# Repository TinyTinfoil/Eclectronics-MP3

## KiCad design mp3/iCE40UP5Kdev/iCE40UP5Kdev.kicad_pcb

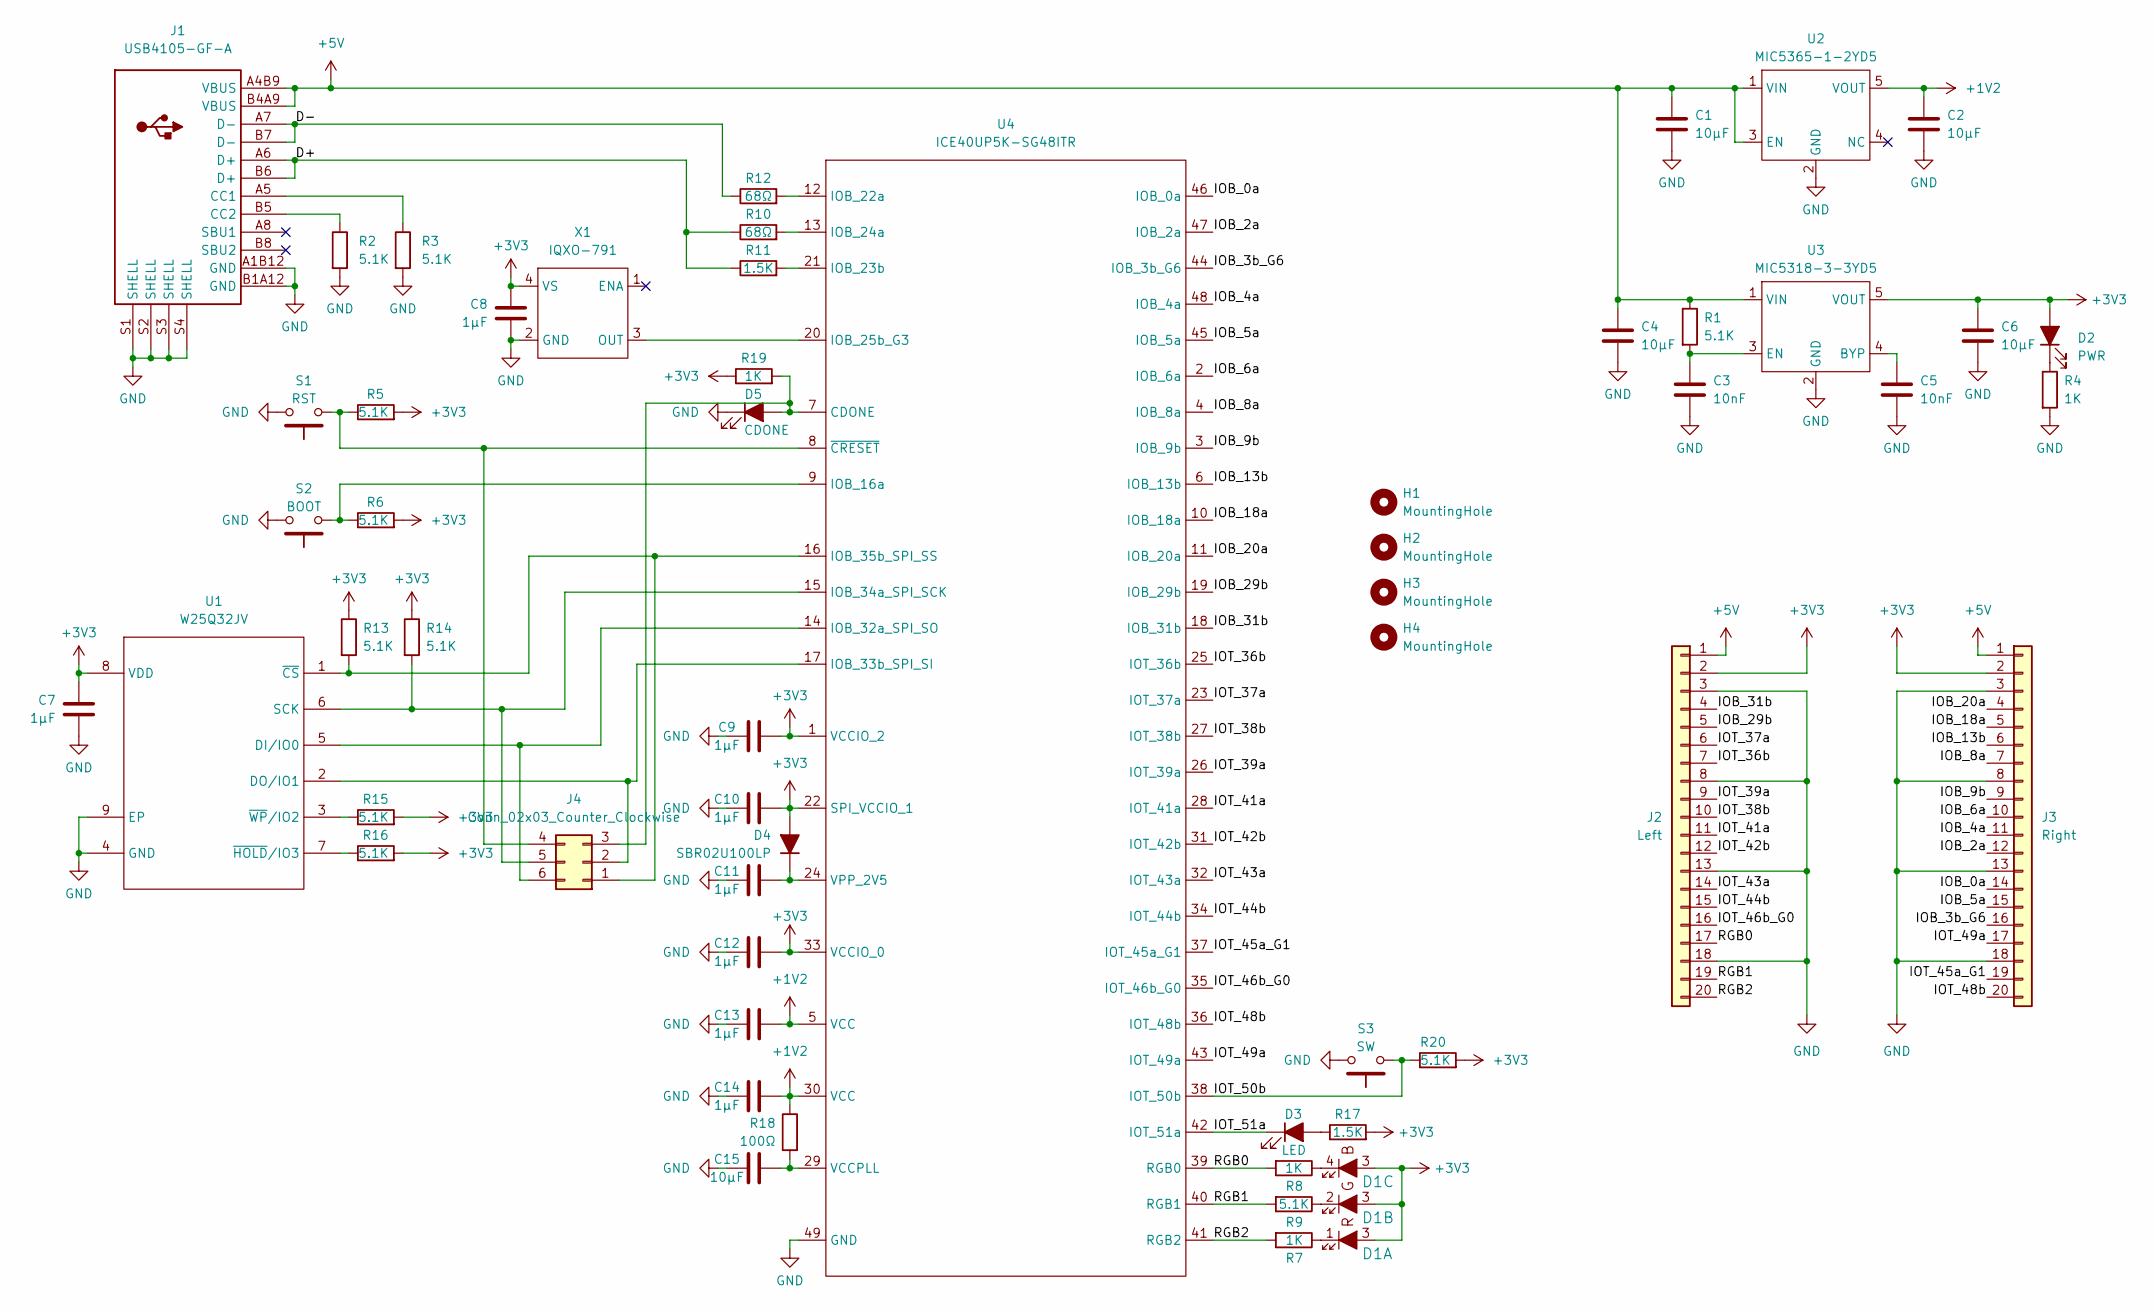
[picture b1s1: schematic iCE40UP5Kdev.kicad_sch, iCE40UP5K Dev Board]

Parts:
C1, C2, C4, C6, C15: 10µF; C_0603_1608Metric
C3, C5: 10nF; C_0402_1005Metric
C7, C8, C9, C10, C11, C12, C13, C14: 1µF; C_0402_1005Metric
D1: IN-S85TATRGB_ALT; IN-S85TATRGB
D2: PWR; LED_0805_2012Metric
D3: LED; LED_0805_2012Metric
D4: SBR02U100LP; D_0402_1005Metric
D5: CDONE; LED_0805_2012Metric
H1, H2, H3, H4: MountingHole; ToolingHole_1.152mm
J1: USB4105-GF-A
J2: Left; PinHeader_1x20_P2.54mm_Vertical
J3: Right; PinHeader_1x20_P2.54mm_Vertical
J4: Conn_02x03_Counter_Clockwise; PinHeader_2x03_P2.54mm_Vertical
R1, R2, R3, R5, R6, R9, R13, R14, R15, R16, R20: 5.1K; R_0402_1005Metric
R4, R7, R8, R19: 1K; R_0402_1005Metric
R10, R12: 68Ω; R_0402_1005Metric
R11, R17: 1.5K; R_0402_1005Metric
R18: 100Ω; R_0402_1005Metric
S1: RST; SW_SPST_B3U-1000P
S2: BOOT; SW_SPST_B3U-1000P
S3: SW; SW_SPST_B3U-1000P
U1: W25Q32JV; WSON-8-1EP_6x5mm_P1.27mm_EP3.4x4.3mm
U2: MIC5365-1-2YD5; TSOT-23-5
U3: MIC5318-3-3YD5; TSOT-23-5
U4: ICE40UP5K-SG48ITR; QFN-48-1EP_7x7mm_P0.5mm_EP5.3x5.3mm
X1: IQXO-791

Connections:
+1V2: C2.1, C13.2, C14.2, R18.1, U2.5 (VOUT), U4.5 (VCC), U4.30 (VCC)
+3V3: C6.1, C7.1, C8.1, C9.2, C10.2, C12.2, D1.3, D2.2 (A), D4.2 (A), J2.2, J3.2, R5.2, R6.2, R13.1, R14.1, R15.2, R16.2, R17.2, R19.1, R20.2, U1.8 (VDD), U3.5 (VOUT), U4.1 (VCCIO_2), U4.22 (SPI_VCCIO_1), U4.33 (VCCIO_0), X1.4 (VS)
+5V: C1.1, C4.1, J1.A4B9 (VBUS), J1.B4A9 (VBUS), J2.1, J3.1, R1.1, U2.1 (VIN), U2.3 (EN), U3.1 (VIN)
/D+: J1.A6 (D+), J1.B6 (D+), R10.1, R11.1
/D-: J1.A7 (D-), J1.B7 (D-), R12.1
/IOB_0a: J3.14, U4.46 (IOB_0a)
/IOB_2a: J3.12, U4.47 (IOB_2a)
/IOB_3b_G6: J3.16, U4.44 (IOB_3b_G6)
/IOB_4a: J3.11, U4.48 (IOB_4a)
/IOB_5a: J3.15, U4.45 (IOB_5a)
/IOB_6a: J3.10, U4.2 (IOB_6a)
/IOB_8a: J3.7, U4.4 (IOB_8a)
/IOB_9b: J3.9, U4.3 (IOB_9b)
/IOB_13b: J3.6, U4.6 (IOB_13b)
/IOB_18a: J3.5, U4.10 (IOB_18a)
/IOB_20a: J3.4, U4.11 (IOB_20a)
/IOB_29b: J2.5, U4.19 (IOB_29b)
/IOB_31b: J2.4, U4.18 (IOB_31b)
/IOT_36b: J2.7, U4.25 (IOT_36b)
/IOT_37a: J2.6, U4.23 (IOT_37a)
/IOT_38b: J2.10, U4.27 (IOT_38b)
/IOT_39a: J2.9, U4.26 (IOT_39a)
/IOT_41a: J2.11, U4.28 (IOT_41a)
/IOT_42b: J2.12, U4.31 (IOT_42b)
/IOT_43a: J2.14, U4.32 (IOT_43a)
/IOT_44b: J2.15, U4.34 (IOT_44b)
/IOT_45a_G1: J3.19, U4.37 (IOT_45a_G1)
/IOT_46b_G0: J2.16, U4.35 (IOT_46b_G0)
/IOT_48b: J3.20, U4.36 (IOT_48b)
/IOT_49a: J3.17, U4.43 (IOT_49a)
/IOT_50b: R20.1, S3.1, U4.38 (IOT_50b)
/IOT_51a: D3.1 (K), U4.42 (IOT_51a)
/RGB0: J2.17, R8.2, U4.39 (RGB0)
/RGB1: J2.19, R9.2, U4.40 (RGB1)
/RGB2: J2.20, R7.2, U4.41 (RGB2)
GND: C1.2, C2.2, C3.2, C4.2, C5.2, C6.2, C7.2, C8.2, C9.1, C10.1, C11.1, C12.1, C13.1, C14.1, C15.1, D5.1 (K), J1.A1B12 (GND), J1.B1A12 (GND), J1.S1 (SHELL), J1.S2 (SHELL), J1.S3 (SHELL), J1.S4 (SHELL), J2.3, J2.8, J2.13, J2.18, J3.3, J3.8, J3.13, J3.18, R2.2, R3.2, R4.2, S1.2, S2.2, S3.2, U1.4 (GND), U1.9 (EP), U2.2 (GND), U3.2 (GND), U4.49 (GND), X1.2 (GND)
unnamed: D1.1, R7.1
unnamed: D1.2, R9.1
unnamed: D1.4, R8.1
unnamed: D2.1 (K), R4.1
unnamed: D3.2 (A), R17.1
unnamed: C11.2, D4.1 (K), U4.24 (VPP_2V5)
unnamed: D5.2 (A), J4.3, R19.2, U4.7 (CDONE)
unnamed: J1.A5 (CC1), R3.1
unnamed: J1.B5 (CC2), R2.1
unnamed: J4.1, R13.2, U1.1 (~CS), U4.16 (IOB_35b_SPI_SS)
unnamed: J4.2, U1.2 (DO/IO1), U4.17 (IOB_33b_SPI_SI)
unnamed: J4.4, R5.1, S1.1, U4.8 (~CRESET)
unnamed: J4.5, R14.2, U1.6 (SCK), U4.15 (IOB_34a_SPI_SCK)
unnamed: J4.6, U1.5 (DI/IO0), U4.14 (IOB_32a_SPI_SO)
unnamed: R16.1, U1.7 (~HOLD/IO3)
unnamed: R15.1, U1.3 (~WP/IO2)
unnamed: C5.1, U3.4 (BYP)
unnamed: C3.1, R1.2, U3.3 (EN)
unnamed: R6.1, S2.1, U4.9 (IOB_16a)
unnamed: R12.2, U4.12 (IOB_22a)
unnamed: R11.2, U4.21 (IOB_23b)
unnamed: R10.2, U4.13 (IOB_24a)
unnamed: U4.20 (IOB_25b_G3), X1.3 (OUT)
unnamed: C15.2, R18.2, U4.29 (VCCPLL)

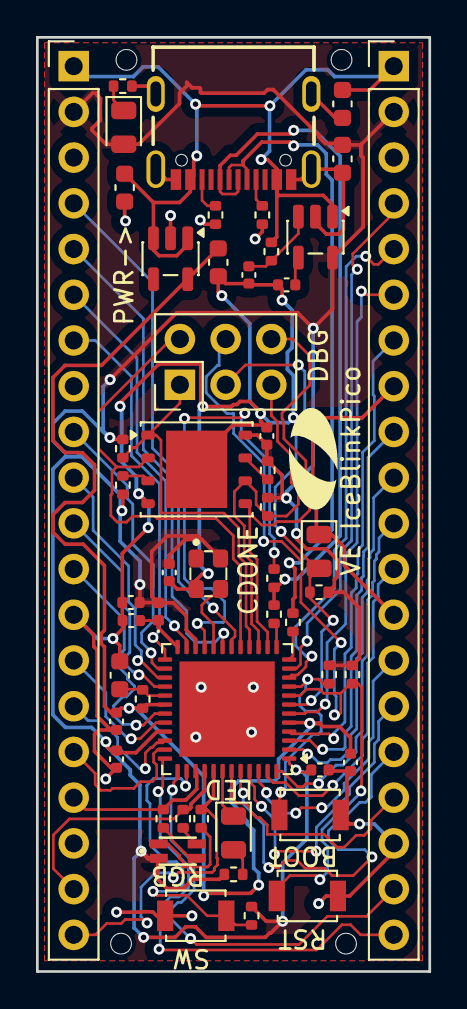
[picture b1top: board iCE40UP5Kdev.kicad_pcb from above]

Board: 2 copper layers, 21.8 x 51.9 mm, 57 parts (0 on the bottom side), 60 nets.

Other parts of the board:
OlinLogo: G***; OlinLogo

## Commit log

2026-03-09 inital commit
2026-03-10 update via spacing
2026-03-10 fix gaps in power pour
